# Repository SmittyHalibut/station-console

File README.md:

# station-console
A station console, to connect an operator, logger, and radio together

This branch (v1-eagle) is the first version I made of the console.

**IT IS BROKEN!  DO NOT BUILD AS IT IS!!**

~Unfortunately, I can't remember what is broke, I built it 5 years ago.
So instead, I'll describe what the INTENTION was, and let you figure it out.~

**I REMEMBER!** When connected to power, it would brown out the supply and draw
as much current as possible. I just debugged it and figured out that I wired the
2.1mm barrel plug backwards!  Oops.  So I'm going to remove the barrel plugs, 
solder wires in their place, and put Anderson Powerpoles at the end of the wire.

# Goals:
* Allow an operator and a logger to both have headsets on and use an HF radio.
* Audio outputs are mixed, with individual volume knobs for each input:
  * Audio into the mic port on the radio is mixed from the operator and loggers's mics.
  * Audio into the operator and loggers headsets is mixed from eachothers' mics,
    and the speaker audio from the radio.
  * Audio into the external speaker is from the speaker audio from the radio.
* All inputs have a simple VU meter (two LEDs) to set input levels.  
* Audio connections to the radio are transformer isolated, so no ground loops.
* Audio connections to the head sets and external speaker are on the console ground,
  which is tied to power ground.
* PTT is not handled by this mixer console at all. PTT must be routed externally.

# Build:
These files are from an old version of Eagle, circa 2015.  I don't use Eagle anymore,
so I can't update the files.  You're on your own for any conversions.

You might be able to fabricate the board as it is and wire your own power in, leaving
off the 2.1mm barrel plug.

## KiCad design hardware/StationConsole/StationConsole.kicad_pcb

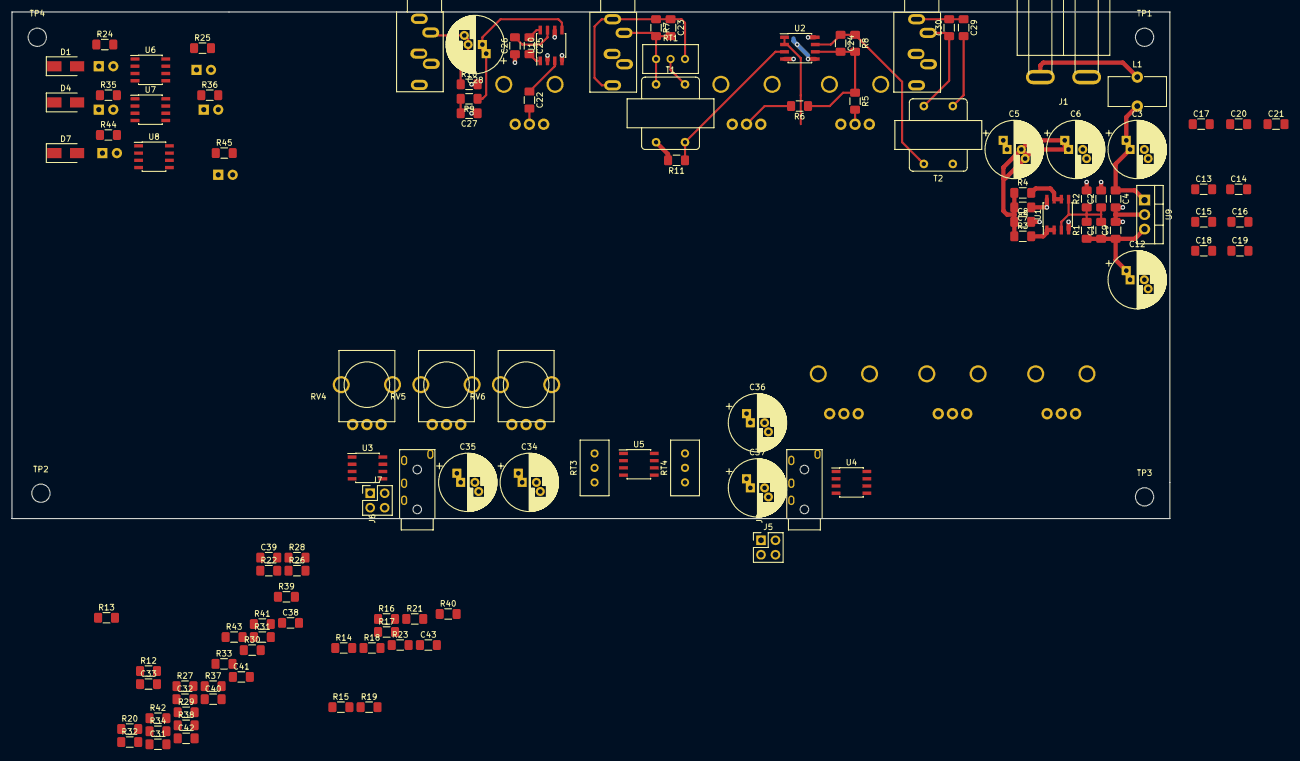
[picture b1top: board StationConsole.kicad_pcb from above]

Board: 4 copper layers, 203.2 x 88.9 mm, 134 parts (0 on the bottom side), 79 nets.

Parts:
C1, C2, C4, C7, C8, C9, C31, C38, C39, C40, C41: 1uF; C_1206_3216Metric_Pad1.42x1.75mm_HandSolder
C3, C5, C6, C12, C28, C34, C35, C36, C37: 220uF; CP_Radial_D10.0mm_P2.50mm_P5.00mm
C10, C11, C13, C14, C15, C16, C17, C18, C19, C20, C21, C22, C23, C24, C26, C27: .1uF; C_1206_3216Metric_Pad1.42x1.75mm_HandSolder
C25: Gain; C_1206_3216Metric_Pad1.42x1.75mm_HandSolder
C29: 10uF; C_1206_3216Metric_Pad1.42x1.75mm_HandSolder
C30: 1nF; C_1206_3216Metric_Pad1.42x1.75mm_HandSolder
C32, C33: 330pF; C_1206_3216Metric_Pad1.42x1.75mm_HandSolder
C42, C43: .01uF; C_1206_3216Metric_Pad1.42x1.75mm_HandSolder
D1, D4, D7: 1N4148; D_SMA
D2, D5, D8: Red; LED_D3.0mm
D3, D6, D9: Green; LED_D3.0mm
J1: 12vDC In; AndersonPP45
J2: Radio Speaker; Conn-3.5mm-SJ1-3535NG
J3: Speaker; Conn-3.5mm-SJ1-3535NG
J4: Radio Mic; Conn-3.5mm-SJ1-3535NG
J5: Log CTIA/OMTP; PinHeader_2x02_P2.54mm_Vertical
J6: Operator Headset; Conn-3.5mm-TRRS-PJ-320L
J7: Op CTIA/OMTP; PinHeader_2x02_P2.54mm_Vertical
J8: Logger Headset; Conn-3.5mm-TRRS-PJ-320L
L1: RF Choke; L_Toroid_Vertical_L10.0mm_W5.0mm_P5.08mm
R1, R2, R5, R6, R10, R15, R16, R17, R18, R19, R20, R26, R27, R28, R29, R37, R38: 10k; R_1206_3216Metric_Pad1.42x1.75mm_HandSolder
R3, R4, R30, R31, R32, R33: 1; R_1206_3216Metric_Pad1.42x1.75mm_HandSolder
R7, R8, R40, R41: 100; R_1206_3216Metric_Pad1.42x1.75mm_HandSolder
R9: 10; R_1206_3216Metric_Pad1.42x1.75mm_HandSolder
R11, R24, R25, R35, R36, R42, R43, R44, R45: 1k; R_1206_3216Metric_Pad1.42x1.75mm_HandSolder
R12: 36k; R_1206_3216Metric_Pad1.42x1.75mm_HandSolder
R13, R14: 4.7k; R_1206_3216Metric_Pad1.42x1.75mm_HandSolder
R21, R34, R39: 100k; R_1206_3216Metric_Pad1.42x1.75mm_HandSolder
R22, R23: 30k; R_1206_3216Metric_Pad1.42x1.75mm_HandSolder
RT1: 1k; Potentiometer_Bourns_3296W_Vertical
RT3, RT4: 10k; Potentiometer_Bourns_3296W_Vertical
RV1, RV2, RV3, RV4, RV5, RV6, RV7, RV8, RV9: 10k; Pot-EVU-F2M
T1, T2: Transformer_AUDIO; AudioTransformer-4pin
TP1, TP2, TP3, TP4: Mount Hole; MountingHole_3.2mm_M3
U1, U3, U4: NJM4556A; SOIC-8_3.9x4.9mm_P1.27mm
U2, U5: NJM2068D; SOIC-8_3.9x4.9mm_P1.27mm
U6, U7, U8: LM393; SOIC-8_3.9x4.9mm_P1.27mm
U9: LM7809_TO220; TO-220-3_Vertical
U10: LM386; SOIC-8_3.9x4.9mm_P1.27mm

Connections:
+9V: C1.1, C5.1, C7.1, C9.1, C10.1, C12.1, C13.1, C15.1, C17.1, C18.1, C20.1, C21.1, R1.1, R12.1, R24.1, R25.1, R35.1, R36.1, R37.2, R38.2, R44.1, R45.1, U1.8, U2.8, U3.8, U4.8, U5.8, U6.8, U7.8, U8.8, U9.3, U10.6
+12V: C3.1, C4.1, L1.2, U9.1
GNDA: C5.2, C6.1, C7.2, C8.1, C10.2, C11.1, C13.2, C14.1, C15.2, C16.1, C18.2, C19.1, C31.1, C38.1, C41.1, R3.1, R4.1, R11.2, R14.2, R21.2, R34.2, R39.2, R40.2, R41.2, RT3.3, RT4.3, RV1.3, RV2.3, RV3.3, RV4.3, RV5.3, RV6.3, RV7.3, RV8.3, RV9.3, T1.3, T2.2, U2.5, U3.3, U4.3
GNDPWR: C2.2, C3.2, C4.2, C6.2, C8.2, C9.2, C11.2, C12.2, C14.2, C16.2, C17.2, C19.2, C20.2, C21.2, C26.1, C27.1, J1.2, J3.S, J5.3, J7.3, R2.2, R10.2, R26.1, R27.1, R28.1, R29.1, U1.4, U2.4, U3.4, U4.4, U5.4, U6.4, U7.4, U8.4, U9.2, U10.2, U10.4
Green: R13.2, R14.1, U6.5, U7.5, U8.5
LogBus: C43.1, D4.2, R43.2, RV2.1, RV5.1, RV8.1, U5.7
LogMic: C40.2, J5.2, R38.1
LogR2: J5.1, J8.R2
LogS: J5.4, J8.S
unnamed: C1.2, C2.1, R1.2, R2.1, U1.3, U1.5
unnamed: C22.1, U10.3
unnamed: C22.2, RV3.2
unnamed: C23.1, J2.S, J2.TN, R7.1, RT1.1
unnamed: C23.2, J2.T, R7.2, RT1.3, T1.2
unnamed: C24.1, R8.1, T2.1, U2.7
unnamed: C24.2, R5.1, R6.1, R8.2, U2.6
unnamed: C25.1, U10.8
unnamed: C25.2, U10.1
unnamed: C26.2, U10.7
unnamed: C27.2, R9.2
unnamed: C28.1, R9.1, U10.5
unnamed: C28.2, J3.T, R10.1
unnamed: C29.1, C30.2, J4.S
unnamed: C29.2, T2.3
unnamed: C30.1, J4.T, T2.4
unnamed: C31.2, D1.1, R21.1, U6.2, U6.6
unnamed: C32.1, C34.1, R22.1, U3.1, U3.5
unnamed: C32.2, R15.1, R16.1, R17.1, R22.2, U3.2
unnamed: C33.1, C36.1, R23.1, U4.1, U4.5
unnamed: C33.2, R18.1, R19.1, R20.1, R23.2, U4.2
unnamed: C34.2, R26.2, R30.1
unnamed: C35.1, U3.6, U3.7
unnamed: C35.2, R28.2, R31.1
unnamed: C36.2, R27.2, R32.1
unnamed: C37.1, U4.6, U4.7
unnamed: C37.2, R29.2, R33.1
unnamed: C38.2, D4.1, R34.1, U7.2, U7.6
unnamed: C39.1, RT3.1
unnamed: C40.1, RT4.1
unnamed: C41.2, D7.1, R39.1, U8.2, U8.6
unnamed: C42.2, R40.1, R42.1, U5.2
unnamed: C43.2, R41.1, R43.1, U5.6
unnamed: D2.1, U6.1
unnamed: D2.2, R24.2
unnamed: D3.1, U6.7
unnamed: D3.2, R25.2
unnamed: D5.1, U7.1
unnamed: D5.2, R35.2
unnamed: D6.1, U7.7
unnamed: D6.2, R36.2
unnamed: D8.1, U8.1
unnamed: D8.2, R44.2
unnamed: D9.1, U8.7
unnamed: D9.2, R45.2
unnamed: J1.1, L1.1
unnamed: J6.R1, R31.2
unnamed: J6.T, R30.2
unnamed: J8.R1, R33.2
unnamed: J8.T, R32.2
unnamed: R3.2, U1.1, U1.2
unnamed: R4.2, U1.6, U1.7
unnamed: R5.2, RV1.2
unnamed: R6.2, RV2.2
unnamed: R11.1, T1.4, U2.3
unnamed: R15.2, RV4.2
unnamed: R16.2, RV5.2
unnamed: R17.2, RV6.2
unnamed: R18.2, RV7.2
unnamed: R19.2, RV8.2
unnamed: R20.2, RV9.2
unnamed: RT1.2, T1.1
unnamed: RT3.2, U5.3
unnamed: RT4.2, U5.5
OpBus: C42.1, D1.2, R42.2, RV1.1, RV4.1, RV7.1, U5.1
OpMic: C39.2, J7.2, R37.1
OpR2: J6.R2, J7.1
OpS: J6.S, J7.4
RadioBus: D7.2, RV3.1, RV6.1, RV9.1, U2.1, U2.2
Red: R12.2, R13.1, U6.3, U7.3, U8.3

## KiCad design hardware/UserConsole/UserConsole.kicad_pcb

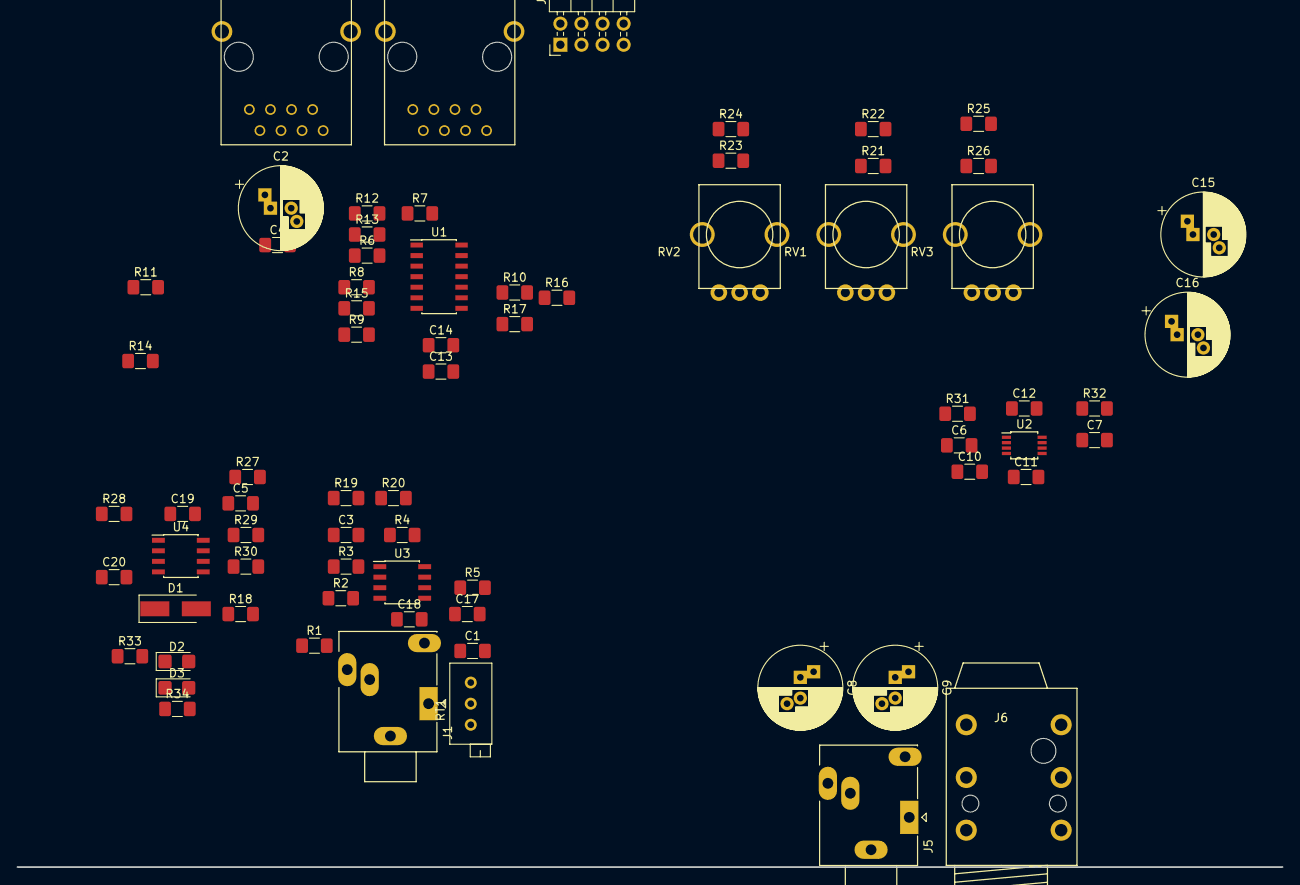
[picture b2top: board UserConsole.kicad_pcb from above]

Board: 2 copper layers, 71 parts (0 on the bottom side), 47 nets, no tracks yet.

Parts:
C1, C4, C5, C10: 1uF; C_1206_3216Metric_Pad1.42x1.75mm_HandSolder
C2, C8, C9, C15, C16: 220uF; CP_Radial_D10.0mm_P2.50mm_P5.00mm
C3, C6, C7: 330pF; C_1206_3216Metric_Pad1.42x1.75mm_HandSolder
C11, C12, C13, C14, C17, C18, C19, C20: .1uF; C_1206_3216Metric_Pad1.42x1.75mm_HandSolder
D1: D_Small; D_SMA_Handsoldering
D2: Red; LED_1206_3216Metric_Castellated
D3: Green; LED_1206_3216Metric_Castellated
J1: Mic; Jack_3.5mm_Ledino_KB3SPRS_Horizontal
J2, J3: Mixer Bus; RJ-45
J4: Operator/Logger; PinHeader_2x04_P2.54mm_Horizontal
J5: Headphones 3.5mm; Jack_3.5mm_Ledino_KB3SPRS_Horizontal
J6: Headphones 1/4"; NRJ6HF
R1, R3, R4, R5, R6, R7, R8, R9, R10, R11, R12, R13, R14, R15, R16, R17, R18, R21, R22, R23, R24, R25, R26, R29, R30, R32: 10k; R_1206_3216Metric_Pad1.42x1.75mm_HandSolder
R2: 100; R_1206_3216Metric_Pad1.42x1.75mm_HandSolder
R19, R20: 10; R_1206_3216Metric_Pad1.42x1.75mm_HandSolder
R27: 100k; R_1206_3216Metric_Pad1.42x1.75mm_HandSolder
R28, R31: 30k; R_1206_3216Metric_Pad1.42x1.75mm_HandSolder
R33, R34: 1k; R_1206_3216Metric_Pad1.42x1.75mm_HandSolder
RT1: 10k; Potentiometer_Bourns_3296X_Horizontal
RV1, RV2, RV3: 10k; Pot-EVU-F2M
U1: TL074; SOIC-14_3.9x8.7mm_P1.27mm
U2: LM4881; TSSOP-8_3x3mm_P0.65mm
U3: TL072; SOIC-8_3.9x4.9mm_P1.27mm
U4: LM393; SOIC-8_3.9x4.9mm_P1.27mm

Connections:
+5V: C2.1, C4.1, C11.1, C13.1, C15.1, C17.1, C19.1, J2.6, J3.6, R1.1, R28.2, U1.4, U2.8, U3.8, U4.8
GNDA: C5.1, C11.2, C12.1, C13.2, C14.1, C15.2, C16.1, C17.2, C18.1, C19.2, C20.1, R2.1, R12.1, R14.1, R16.1, R27.1, R30.1, RT1.3, RV1.3, RV2.3, RV3.3, U1.13, U1.14, U3.5
GNDPWR: C2.2, C4.2, C10.2, C12.2, C14.2, C16.2, C18.2, C20.2, D2.1, D3.1, J1.S, J1.TN, J2.3, J3.3, J5.T, J5.TN, J6.T, J6.TN, U1.11, U2.4, U2.5, U3.4, U4.4
Logger+: J2.7, J3.7, J4.6, R10.2
Logger-: J2.8, J3.8, J4.8, R11.2
unnamed: C1.1, RT1.1
unnamed: C1.2, J1.T
unnamed: C3.1, R3.1, R4.2, R19.2, U3.1
unnamed: C3.2, R2.2, R3.2, U3.2
unnamed: C5.2, D1.1, R27.2, U4.2, U4.6
unnamed: C6.1, C8.1, R31.1, U2.1
unnamed: C6.2, R21.1, R23.1, R25.1, R31.2, U2.2
unnamed: C7.1, C9.1, R32.1, U2.7
unnamed: C7.2, R22.1, R24.1, R26.1, R32.2, U2.6
unnamed: C8.2, J5.R, J6.R
unnamed: C9.2, J5.S, J6.S
unnamed: C10.1, U1.12, U2.3
unnamed: D1.2, R18.1
unnamed: D2.2, R33.1
unnamed: D3.2, R34.1
unnamed: J1.R, R1.2
unnamed: J2.SH, J3.SH
unnamed: J4.1, J4.5, R19.1
unnamed: J4.3, J4.7, R20.1
unnamed: R4.1, R5.2, U3.6
unnamed: R10.1, R16.2, U1.10
unnamed: R11.1, R17.2, U1.9
unnamed: R6.1, R12.2, U1.3
unnamed: R13.1, RV1.1, U1.1
unnamed: R7.1, R13.2, U1.2
unnamed: R8.1, R14.2, U1.5
unnamed: R15.1, RV2.1, U1.7
unnamed: R9.1, R15.2, U1.6
unnamed: R17.1, RV3.1, U1.8
unnamed: R5.1, R18.2, R20.2, U3.7
unnamed: R21.2, R22.2, RV1.2
unnamed: R23.2, R24.2, RV2.2
unnamed: R25.2, R26.2, RV3.2
unnamed: R28.1, R29.2, U4.3
unnamed: R29.1, R30.2, U4.5
unnamed: R33.2, U4.1
unnamed: R34.2, U4.7
unnamed: RT1.2, U3.3
Operator+: J2.5, J3.5, J4.2, R8.2
Operator-: J2.4, J3.4, J4.4, R9.2
Radio+: J2.1, J3.1, R6.2
Radio-: J2.2, J3.2, R7.2

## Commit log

2019-11-27 v1.0 as built in 2015. THIS VERSION IS BROKEN! See README.md
2019-11-27 Update README with intentions for v2.
2019-11-28 Schematic: near exact copy of v1 schematic, but in KiCAD (vs Eagle), removed VU meters, fixed a few things.
2019-11-28 UserConsole is the start of a modular version of this project.
2019-11-28 PDF of the schematic as of 2019-11-28.
2019-11-29 Updated README.md once I remembered what was wrong with this board. It can be hacked around!
2019-11-30 Progress on the PCB.
2020-02-02 https://www.youtube.com/watch?v=d2vIKhrSCEs Split into separate pages. Added block diagram documentation. Started board layout.
